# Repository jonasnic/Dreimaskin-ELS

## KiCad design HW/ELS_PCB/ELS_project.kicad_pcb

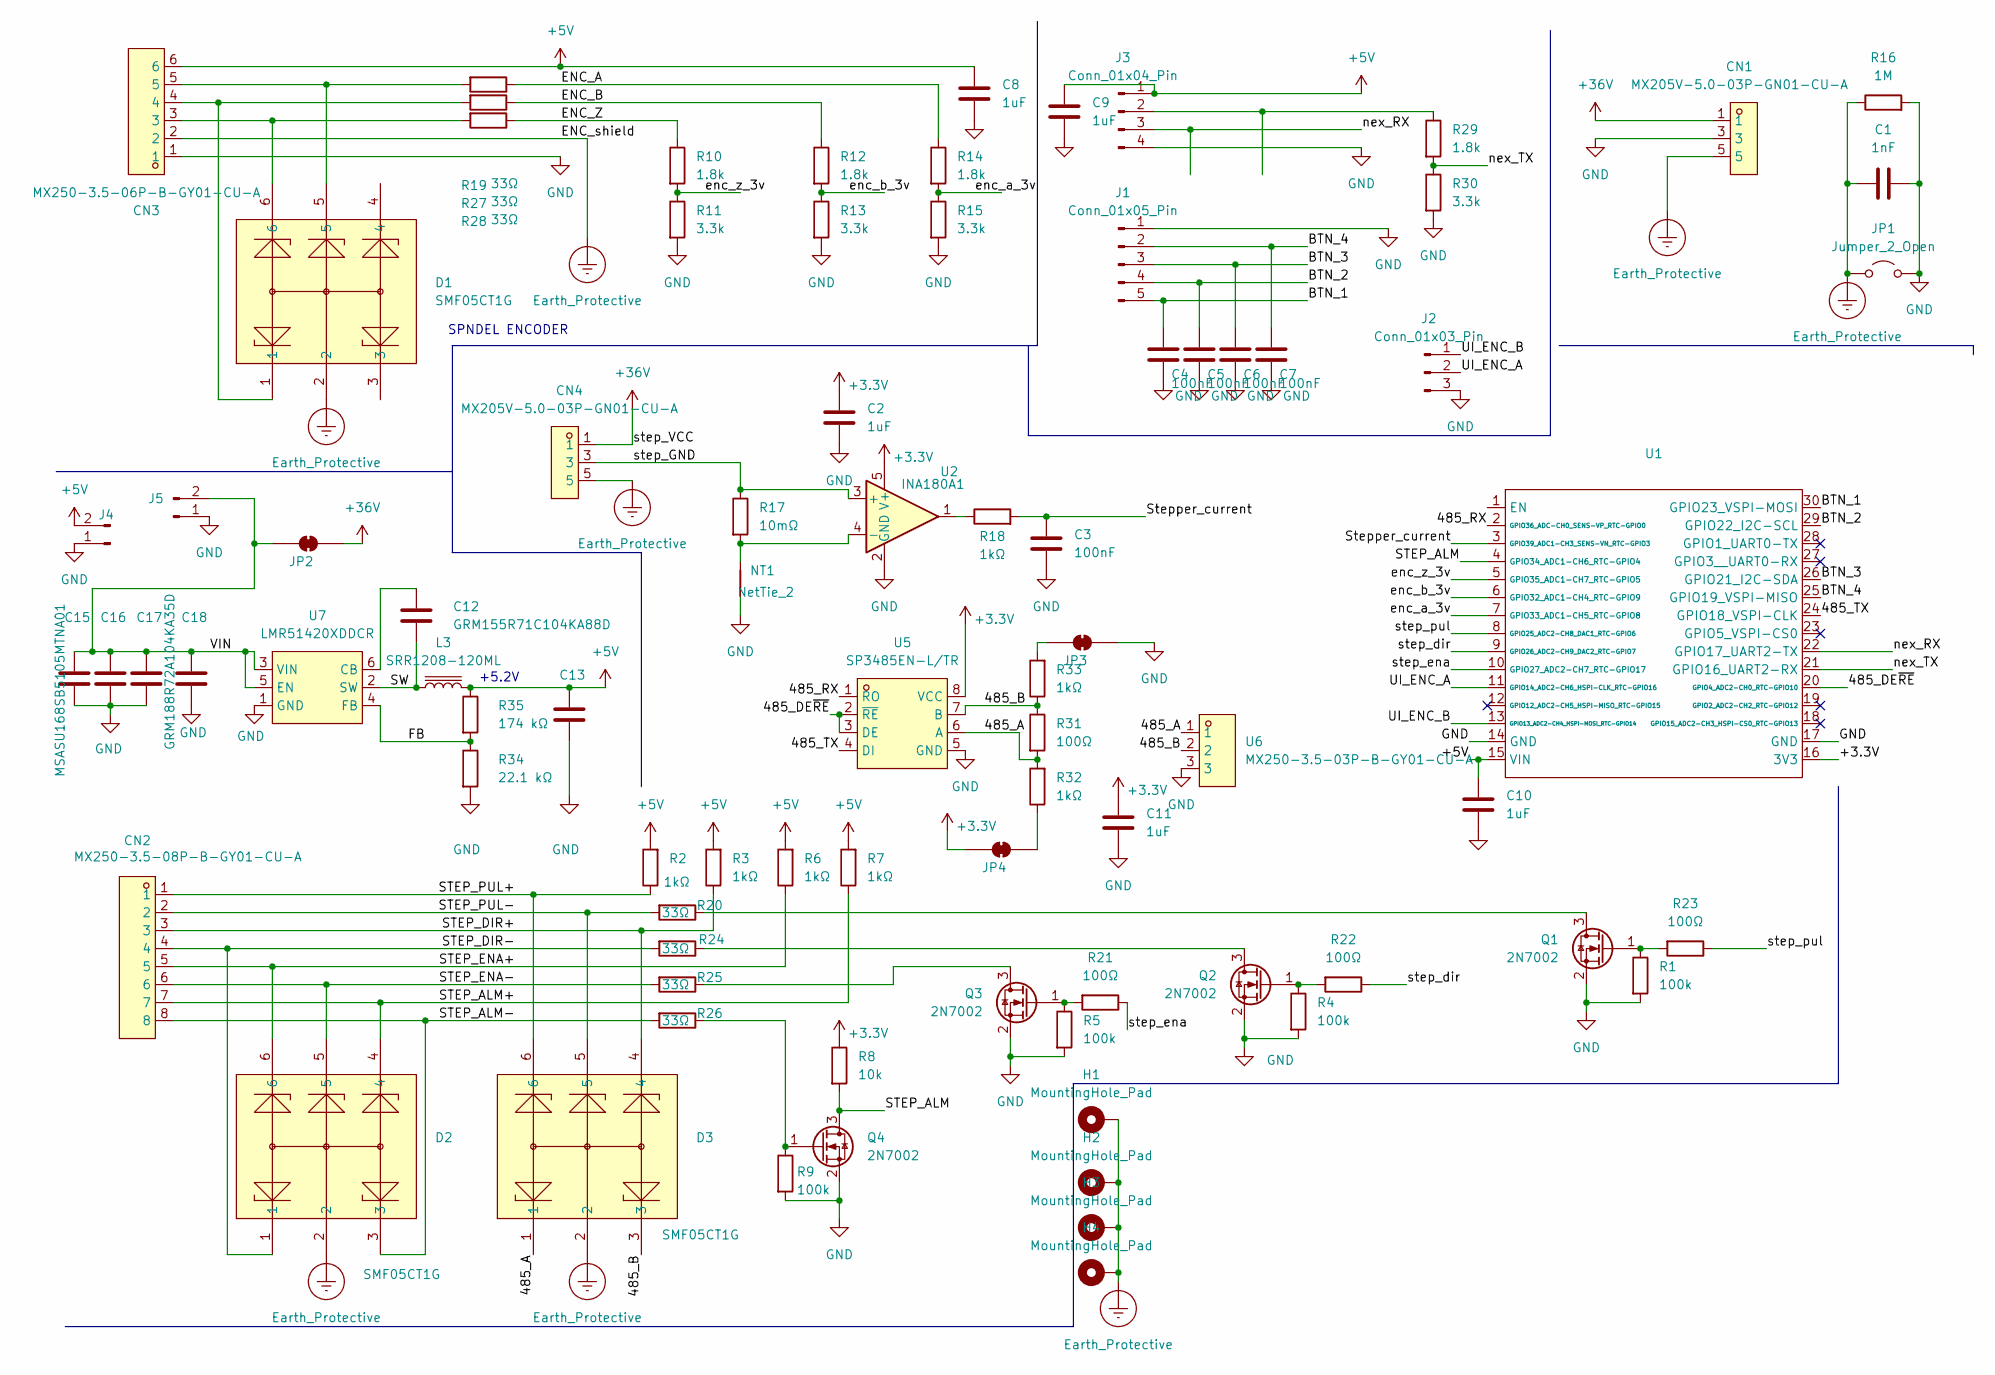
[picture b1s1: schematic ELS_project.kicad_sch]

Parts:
C1: 1nF; C_0402_1005Metric; LCSC C1523
C2, C8, C9, C10, C11: 1uF; C_0402_1005Metric; LCSC C52923
C3, C4, C5, C6, C7: 100nF; C_0402_1005Metric; LCSC C1525
C12: GRM155R71C104KA88D; C_0402_1005Metric
C13: GRM32ER61C476KE15L; C_1210_3225Metric
C15, C16, C17: MSASU168SB5105MTNA01; C_0603_1608Metric
C18: GRM188R72A104KA35D; C_0603_1608Metric
CN1, CN4: MX205V-5.0-03P-GN01-CU-A; CONN-TH_3P-P5.00_MX205V-5.0-03P-GN01-CU-A; MPN MX205V-5.0-03P-GN01-Cu-A; LCSC Part C7471323
CN2: MX250-3.5-08P-B-GY01-CU-A; CONN-TH_8P-P3.50-LS5.10_MX250-3.5-08P-B-GY01-CU-A; MPN MX250-3.5-08P-B-GY01-Cu-A; LCSC Part C7470122
CN3: MX250-3.5-06P-B-GY01-CU-A; CONN-TH_6P-P3.50_MX250-3.5-06P-B-GY01-CU-A; MPN MX250-3.5-06P-B-GY01-Cu-A; LCSC Part C7470120
D1, D2, D3: SMF05CT1G; SOT-363_L2.0-W1.3-P0.65-LS2.1-BR; MPN SMF05CT1G; LCSC Part C15879
H1, H2, H3, H4: MountingHole_Pad; MountingHole_3.2mm_M3_Pad_TopOnly
J1: Conn_01x05_Pin; JST_PH_B5B-PH-K_1x05_P2.00mm_Vertical
J2: Conn_01x03_Pin; JST_PH_B3B-PH-K_1x03_P2.00mm_Vertical
J3: Conn_01x04_Pin; JST_PH_B4B-PH-K_1x04_P2.00mm_Vertical
J4, J5: Conn_01x02_Pin; JST_XH_B2B-XH-AM_1x02_P2.50mm_Vertical
JP1: Jumper_2_Open; TestPoint_2Pads_Pitch2.54mm_Drill0.8mm
JP2, JP3, JP4: SolderJumper_2_Bridged; SolderJumper-2_P1.3mm_Bridged_Pad1.0x1.5mm
L3: SRR1208-120ML; L_Bourns_SRR1208_12.7x12.7mm
NT1: NetTie_2; NetTie-2_SMD_Pad2.0mm
Q1, Q2, Q3, Q4: 2N7002; SOT-23; LCSC C8545
R1, R4, R5, R9: 100k; R_0603_1608Metric; LCSC C25803
R2, R3, R6, R7, R18, R32, R33: 1kΩ; R_0603_1608Metric; LCSC C21190
R8: 10k; R_0603_1608Metric; LCSC C25803
R10, R12, R14, R29: 1.8k; R_0603_1608Metric; LCSC C4177
R11, R13, R15, R30: 3.3k; R_0603_1608Metric; LCSC C22978
R16: 1M; R_0603_1608Metric; LCSC C22935
R17: 10mΩ; R_2512_6332Metric; LCSC C5121042
R19, R20, R24, R25, R26, R27, R28: 33Ω; R_0603_1608Metric; LCSC C23140
R21, R22, R23: 100Ω; R_0603_1608Metric; LCSC C22775
R31: 100Ω; R_0402_1005Metric; LCSC C17437
R34: 22.1 kΩ; R_0402_1005Metric
R35: 174 kΩ; R_0402_1005Metric
U1: ESP32-DEVKIT-V1_30pin
U2: INA180A1; SOT-23-5; LCSC C48533472
U5: SP3485EN-L/TR; SOIC-8_L5.0-W4.0-P1.27-LS6.0-BL; MPN SP3485EN-L/TR; LCSC Part C8963
U6: MX250-3.5-03P-B-GY01-CU-A; CONN-TH_3P-P3.50_MX250-3.5-03P-B-GY01-CU-A; MPN MX250-3.5-03P-B-GY01-Cu-A; LCSC Part C7470117
U7: LMR51420XDDCR; SOT-23-6_L2.9-W1.6-P0.95-LS2.8-BL; MPN LMR51420XDDCR; LCSC Part C5246146

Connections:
+3.3V: C2.2, C11.2, JP4.2 (B), R8.1, U1.16 (3V3), U2.5 (V+), U5.8 (VCC)
+5V: C8.2, C9.2, C10.2, C13.1, CN3.6, J3.1, J4.2, L3.2, R2.2, R3.2, R6.2, R7.2, R35.1, U1.15 (VIN)
+36V: CN1.1, CN1.2, CN4.1, CN4.2, JP2.1 (A)
/485_A: D3.1, R31.2, R32.2, U5.6 (A), U6.1
/485_B: D3.3, R31.1, R33.1, U5.7 (B), U6.2
/485_DE~RE: U1.20 (GPIO4_ADC2-CH0_RTC-GPIO10), U5.2 (~RE), U5.3 (DE)
/485_RX: U1.2 (GPIO36_ADC-CH0_SENS-VP_RTC-GPIO0), U5.1 (RO)
/485_TX: U1.24 (GPIO18_VSPI-CLK), U5.4 (DI)
/BTN_1: C4.2, J1.5, U1.30 (GPIO23_VSPI-MOSI)
/BTN_2: C5.2, J1.4, U1.29 (GPIO22_I2C-SCL)
/BTN_3: C6.2, J1.3, U1.26 (GPIO21_I2C-SDA)
/BTN_4: C7.2, J1.2, U1.25 (GPIO19_VSPI-MISO)
/ENC_A: R14.1, R19.1
/ENC_B: R12.1, R27.1
/ENC_Z: R10.1, R28.1
/FB: R34.1, R35.2, U7.4 (FB)
/STEP_ALM: Q4.3 (D), R8.2, U1.4 (GPIO34_ADC1-CH6_RTC-GPIO4)
/STEP_ALM+: CN2.7, D2.4, R7.1
/STEP_ALM-: CN2.8, D2.3, R26.2
/STEP_DIR+: CN2.3, D3.4, R3.1
/STEP_DIR-: CN2.4, D2.1, R24.2
/STEP_ENA+: CN2.5, D2.6, R6.1
/STEP_ENA-: CN2.6, D2.5, R25.2
/STEP_PUL+: CN2.1, D3.6, R2.1
/STEP_PUL-: CN2.2, D3.5, R20.2
/SW: C12.2, L3.1, U7.2 (SW)
/Stepper_current: C3.2, R18.2, U1.3 (GPIO39_ADC1-CH3_SENS-VN_RTC-GPIO3)
/UI_ENC_A: J2.2, U1.11 (GPIO14_ADC2-CH6_HSPI-CLK_RTC-GPIO16)
/UI_ENC_B: J2.1, U1.13 (GPIO13_ADC2-CH4_HSPI-MOSI_RTC-GPIO14)
/VIN: C15.1, C16.1, C17.1, C18.1, J5.2, JP2.2 (B), U7.3 (VIN), U7.5 (EN)
/enc_a_3v: R14.2, R15.1, U1.7 (GPIO33_ADC1-CH5_RTC-GPIO8)
/enc_b_3v: R12.2, R13.1, U1.6 (GPIO32_ADC1-CH4_RTC-GPIO9)
/enc_z_3v: R10.2, R11.1, U1.5 (GPIO35_ADC1-CH7_RTC-GPIO5)
/nex_RX: J3.3, U1.22 (GPIO17_UART2-TX)
/nex_TX: R29.2, R30.1, U1.21 (GPIO16_UART2-RX)
/step_GND: CN4.3, CN4.4, R17.1, U2.3 (+)
/step_dir: R22.1, U1.9 (GPIO26_ADC2-CH9_DAC2_RTC-GPIO7)
/step_ena: R21.1, U1.10 (GPIO27_ADC2-CH7_RTC-GPIO17)
/step_pul: R23.1, U1.8 (GPIO25_ADC2-CH8_DAC1_RTC-GPIO6)
Earth_Protective: C1.1, CN1.5, CN1.6, CN3.2, CN4.5, CN4.6, D1.2, D2.2, D3.2, H1.1 (1_1), H2.1 (1_1), H3.1 (1_1), H4.1 (1_1), JP1.1 (A), R16.1
GND: C1.2, C2.1, C3.1, C4.1, C5.1, C6.1, C7.1, C8.1, C9.1, C10.1, C11.1, C13.2, C15.2, C16.2, C17.2, C18.2, CN1.3, CN1.4, CN3.1, J1.1, J2.3, J3.4, J4.1, J5.1, JP1.2 (B), JP3.1 (A), NT1.1, Q1.2 (S), Q2.2 (S), Q3.2 (S), Q4.2 (S), R1.2, R4.2, R5.2, R9.2, R11.2, R13.2, R15.2, R16.2, R30.2, R34.2, U1.14 (GND), U1.17 (GND), U2.2 (GND), U5.5 (GND), U6.3, U7.1 (GND)
unnamed: CN3.3, D1.6, R28.2
unnamed: CN3.4, D1.1, R27.2
unnamed: CN3.5, D1.5, R19.2
unnamed: J3.2, R29.1
unnamed: JP3.2 (B), R33.2
unnamed: JP4.1 (A), R32.1
unnamed: Q1.3 (D), R20.1
unnamed: Q1.1 (G), R1.1, R23.2
unnamed: Q2.3 (D), R24.1
unnamed: Q2.1 (G), R4.1, R22.2
unnamed: Q3.3 (D), R25.1
unnamed: Q3.1 (G), R5.1, R21.2
unnamed: Q4.1 (G), R9.1, R26.1
unnamed: R18.1, U2.1
unnamed: NT1.2, R17.2, U2.4 (-)
unnamed: C12.1, U7.6 (CB)

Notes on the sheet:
+5.2V
SPNDEL ENCODER

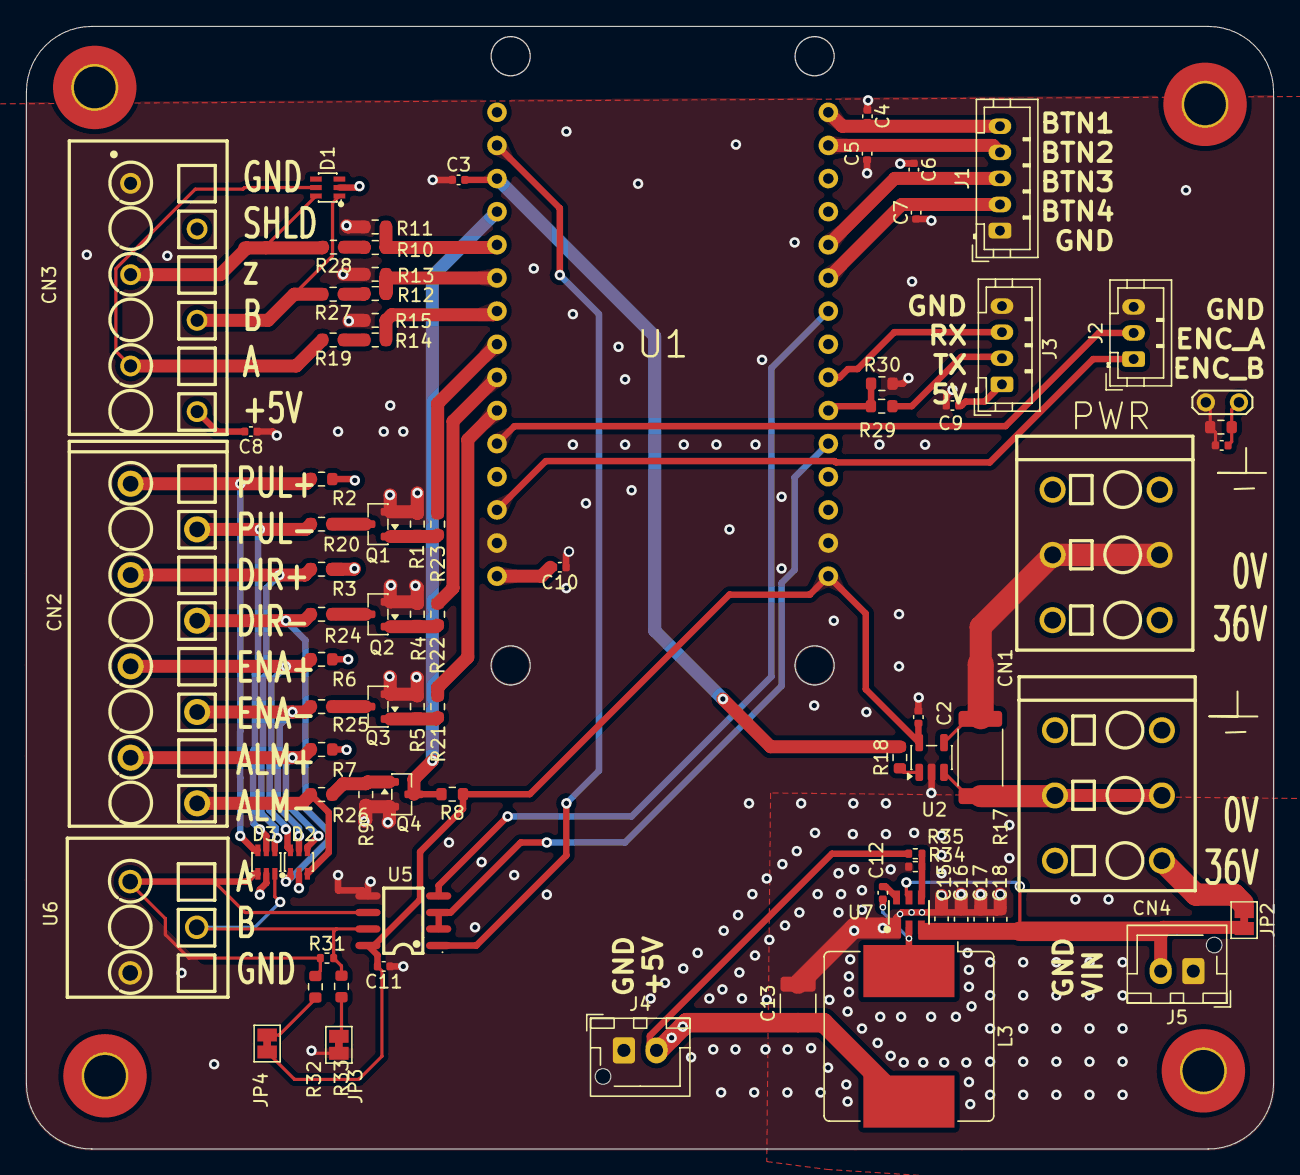
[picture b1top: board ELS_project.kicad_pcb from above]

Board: 4 copper layers, 95.6 x 86.1 mm, 83 parts (0 on the bottom side), 57 nets.

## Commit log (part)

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2026-04-02 Initial Stepper Works
2026-04-02 added the intial logic for the spindel driving
2026-04-03 Implement stepper motor control and encoder setup with RMT integration
2026-04-04 Adjust maximum speed and deceleration parameters for stepper motor control
2026-04-04 initial splitting works. can send data from UI task to motion task
2026-04-04 Refactor motion control and RMT setup: - Update setupRMT function to include a callback parameter. - Enhance motionTask to manage current position and target movement. - Introduce utility functions f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
2026-04-05 Adjust stepper motor parameters and enhance motion control logic
    todo: move dir_change to inside updatespeed to make sure i do it when its stopped
2026-04-05 minor cleanup
2026-04-05 Implement MQTT and WiFi management tasks;
2026-04-06 Refactor motion control logic to use ping-pong buffers and improve task notification handling
2026-04-06 Enhance motion control parameters and add target status publishing
2026-04-07 Enhance motion control and MQTT integration
    - Increased pulse high time from 2 to 4 microseconds for improved motion control.
    - Added new functions in mqtt_manager.h for publishing motion mode and motion data.
    - Implemented mode command parsing in ui_task.cpp to handle motion mode changes.
    - Updated mqtt_manager.cpp to handle new MQTT topics for motion mode and distance to target.
    - Refactored motion_task.cpp to support motion batching and improved motion planning.
    - Enhanced queues.h to include new motion data types and commands.
2026-04-07 Add plotting functionality for speed and motion data in MQTT GUI
2026-04-08 Implement dual-buffering system for RMT with enhanced buffer loading functions
2026-04-08 some foramting. mainly fixed how to fill the buffer. and changed the rmt setup/start
2026-04-08 Refactor motion control and RMT setup for improved buffer handling and task management
2026-04-10 This is a basic working version
2026-04-10 just added the exel i just to make the bitpatern
2026-04-10 removed old file
2026-04-10 project cleanup. put all code in software folder. i can now make folder for hw
2026-04-12 started a kicadproject
    Add ESP32 Dev V1 symbol and associated library files
    - Created a new symbol library for the ESP32_DEV_V1 component, including properties for Reference, Value, Footprint, Datasheet, and Description.
    - Added a footprint library table entry for the ESP32 development kit.
    - Updated the symbol library table to include the new ESP32_DEV_V1 symbol and a legacy library entry.
2026-04-13 ordered the PCB
2026-04-13 Refactor motion_task.h and motion_task.cpp to use constexpr for constants and improve speed calculation logic
2026-04-21 Refactor encoder and motion task logic to improve accuracy and performance; add current sensor functionality
2026-04-28 Refactor motion control and enhance UI integration
    - Updated motion_task.cpp to improve motion handling and direction control.
    - Introduced new RMT functions in rmt.cpp for better pulse generation and buffer management.
    - Modified utils.cpp and utils.h to support signed frequency handling.
    - Enhanced the MQTT GUI in app.py to include controls for stepper enable/disable and pitch settings.
    - Added new status indicators for RPM, alarm state, loop time, and batch time in the GUI.
    - Improved data reporting and handling of UI updates in motion_task.cpp.
2026-04-28 redesigned the powerstage sinse the org got realy hot. using newer parts
2026-04-28 Refactor motion control configuration and remove step counter implementation; introduce config.h for constants and update rate management
2026-04-28 Add new Excel file for data analysis and reporting
2026-05-03 Add FreeCAD project files and update MQTT management
    - Added new FreeCAD project files: ELS_project.FCStd, button.FCStd, encoder2.FCStd, and nextion_simp.FCStd along with their backup versions.
    - Refactored MQTT management in mqtt_manager.h and mqtt_manager.cpp:
    - Removed legacy task creation function and replaced it with a non-blocking service tick function.
    - Improved connection handling and initialization logic.
    - Updated reconnect interval to 3000 ms.
    - Enhanced command subscription handling using an array.
2026-05-05 nyBox
